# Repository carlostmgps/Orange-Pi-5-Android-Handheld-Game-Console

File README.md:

# Orange-Pi-5-Handheld-Game-Console
Orange Pi 5 + Battery + Touch Screen + Microphone + Speaker + Fan + esp32 Custom PCB controller = AMAZING ANDROID AND LINUX GAME CONSOLE!!!!!!!

Hello I'm 12zcab,a secondary school student in HK.

# why I made this project?
Welp I'm a really big fan of retro gaming such as n64, gameboy, nes,gba(oh yah I loved Nintendo.) why? That's mainly because one day I found a few old books on a table near my home labeled "Free",and I took it home and read all of it.
Theres one that caused me to be a retro fan,an user manual of Hektor,a 8085 computer.After reading that book,I discovered Zilog80,an amazing and neat perfect and the easiest design I have ever seen.
You know what? Actually the Nintendo Gameboy's instruction set is really similar to Zilog80 and I started to research on how gameboy works and I even made my "own gameboy emulator" by searching how it works online and copy some of other's code then add more function myself.
Also I like to read code of the disassembled version of gameboy game Pokémon Red.
And now I really wanna make my own game console with orange pi that can emulate the Nintendo Game Console Series from NES to NDS.

# 3/7/2026 Day 1
 12:35pm
I just discovered the blueprint scheme a few days ago and now I realized,its the time to make my dream game console come true.
There are only 2 weeks left for me but I think i can make it in time.
So firstly my planned hardware should include:
1 Orange Pi 5 16gb ram    for games like MineCraft and emulators like RETROARCH
1 touchscreen
1 speaker ...or maybe 2?
1 Microphone
1 simple tiny fan to cool down my CM5
2 D1mini for my custom PCB comtroller
2 Joysticks
IDK A few buttons
Some Batteries

My goal:
1.Use linux to run minecraft Java
2.Use retroarch to emulate NDS Games

USB Battery Pack for Raspberry Pi - 10000mAh - 2 x 5V outputs  [LINK](https://www.adafruit.com/product/1566) 39.95USD
Orange Pi 5 16gb [Link](https://e.tb.cn/h.i2LfNGjXf5lZXff?tk=K51dUuX3cC2)  1900 rmb
2x 64gb tfcard [LINK](https://e.tb.cn/h.i2ybQZQlsHyMiE1?tk=S8PhUuRI9QB)  140rmb
7inch touchscreen [Link](https://e.tb.cn/h.i2RoroSwYrMQFAG?tk=mAtMUuRFne7) 198rmb
Cooling Fan 19rmb [LINK](https://e.tb.cn/h.idzK3fJlqxSjamQ?tk=dNAvUuRyINo)

Then I started designing my d1mini joycon😜😜(18:25pm)

Erm yah I just wired the power supply and watched some youtube and now is 23:58pm and I guess I gotta sleep.

# Day 2 8-3-2026  17:35
Humm I decided to use esp32 C3 supermini board I found in taobao as it's much smaller.
However...I really can't find a Kicad module so I use Conn_MMxNN to represent the board.
23:45 YEAH~~~~ I think this kinda good i guess

12:49am gotta sleep :/ I just finished routing the pcb😁😁

# Day 3 9-3-2026
Continued on pcb editing and searched for material needed in taobao website.

Also I hope I can finish the pcb design in 3 to 4days and prepare the material list in a week then start to design the case.
Hopefully I can submit the project for review before 23-3-2026.

# Day 6 12-3-2026
I just done a simple bom list and finished all the pcb designing(oh yeah it's name was d1mini joycon as I originally wanted to use d1mini but found out it only have 1 analog pin) (yay!) All files including the stl file can be found in the PCB-Design folder in github.
Erm because I'm lazy so I think i will just simply flip the board for another side hehe.
Also I just did some research on using esp32 to make controllers and I tried it with d1mini and it's perfect:D

# Day 11 17-3-2026
HUMMMMMMMM I hope this 3D model is okay I guess. Im not really good at designing.

The 3D model is uploaded to the Model file,but sadly i cant really share the original file cuz its made with tinkercad.
[LINK to TINKERCAD Project](https://www.tinkercad.com/things/lrAWRHE2oKm-orangepi-game-console?sharecode=MQfT5zH1kE5UchqxLdm9KHmoapcb7OkEz_jWbnckgjE)

# Day 13 19-3-2026
YAY i just done the firmware,however the usage of S and S2 button and Mode button and LED is not yet decided yet :D
I have made two different firmware files,for arduino and micropython.
Actually I'm not really good at arduino CPP coding but i think it does save more memory incase i wanna make a macro function to record my move and save them which may use a lot of memory?
[LINK to the firmware file](https://github.com/carlostmgps/Orange-Pi-5-Android-Handheld-Game-Console/tree/main/firmware)

Erm the submission is reject then I think i will try to save money and buy the orange pi myself later 😅😅
I deleted the orange pi and it's fan from bom and tried to resubmit:D

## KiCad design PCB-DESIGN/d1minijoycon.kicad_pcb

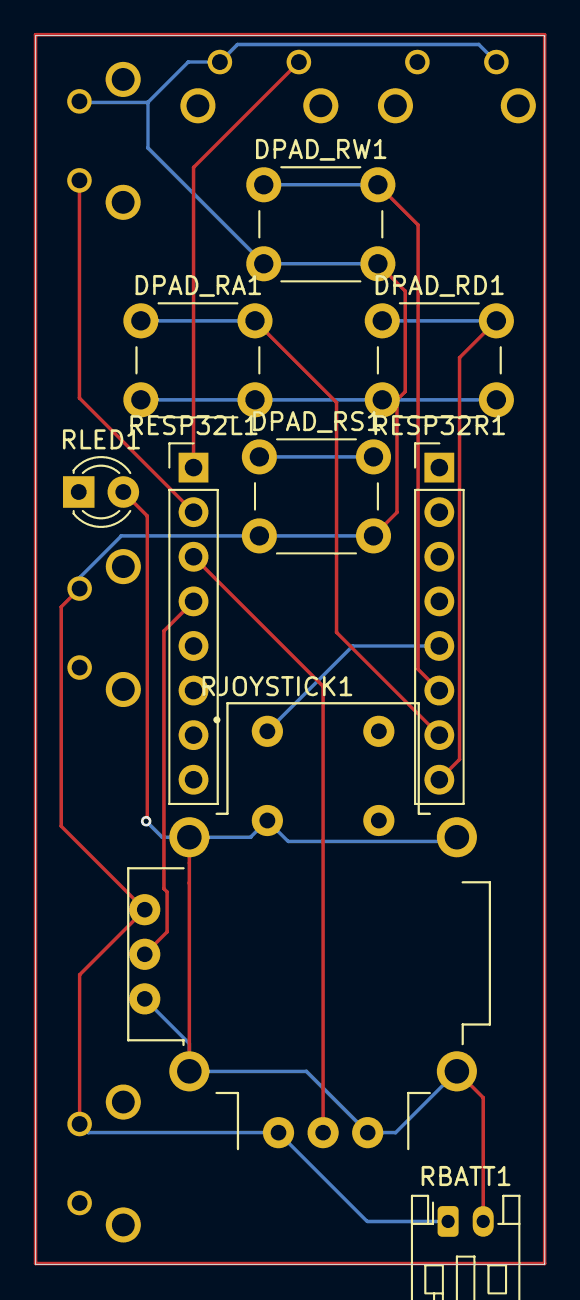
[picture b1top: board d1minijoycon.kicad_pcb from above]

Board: 2 copper layers, 29.0 x 70.0 mm, 14 parts (0 on the bottom side), 10 nets.

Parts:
DPAD_RA1: A; SW_PUSH_6mm_H5mm
DPAD_RD1: D; SW_PUSH_6mm_H5mm
DPAD_RS1: S; SW_PUSH_6mm_H5mm
DPAD_RW1: W; SW_PUSH_6mm_H5mm
R2S1: S2; TACT-6MM-HOR
RBATT1: Conn_01x02; JST_PH_S2B-PH-K_1x02_P2.00mm_Horizontal
RESP32L1, RESP32R1: ESP32 C3 SUPERMINI; PinHeader_1x08_P2.54mm_Vertical
RJOYSTICK1: COM-09032; XDCR_COM-09032
RL1: L; TACT-6MM-HOR
RLED1: LED; LED_D3.0mm
RM1: MODE; TACT-6MM-HOR
RR1: R; TACT-6MM-HOR
RS1: S; TACT-6MM-HOR

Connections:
unnamed: DPAD_RA1.2, DPAD_RD1.2, DPAD_RS1.2, DPAD_RW1.2, R2S1.2, RBATT1.1, RJOYSTICK1.H1 (H+), RJOYSTICK1.V1 (V+), RL1.2, RM1.1, RR1.2, RS1.2
unnamed: RBATT1.2, RJOYSTICK1.B2A (SEL-), RJOYSTICK1.H3 (H-), RJOYSTICK1.S1 (SHIELD), RJOYSTICK1.S2 (SHIELD), RJOYSTICK1.S3 (SHIELD), RJOYSTICK1.S4 (SHIELD), RJOYSTICK1.V3 (V-), RLED1.2 (A)
unnamed: RESP32L1.4, RJOYSTICK1.V2 (V)
unnamed: RESP32L1.3 (Pin_5), RJOYSTICK1.H2 (H)
unnamed: RESP32L1.2 (Pin_6), RR1.1
unnamed: RESP32L1.1 (Pin_7), RM1.2
unnamed: RESP32R1.5 (Pin_1), RJOYSTICK1.B1A (SEL+)
unnamed: DPAD_RW1.1, RESP32R1.6 (Pin_2)
unnamed: DPAD_RA1.1, RESP32R1.7 (Pin_3)
unnamed: DPAD_RD1.1, RESP32R1.8 (Pin_4)

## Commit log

2026-03-08 Rename d1minijoycon.png to image/d1minijoycon.png
2026-03-08 Update README with routed PCB images
    Added images of the routed PCB to the README.
2026-03-09 更新 README.md
2026-03-12 Create EASTEREGGHEHE
2026-03-17 Revise project timeline and add 3D model information
    Updated project timeline and added new sections for Day 11 and 3D model details.
2026-03-17 Rename OrangePi Game Console.stl to Model/OrangePi Game Console.stl
2026-03-17 Create erm another easteregg
2026-03-19 Fix formatting and capitalization in README.md
    Fixed formatting issues in the README file, including spacing and capitalization.
2026-03-19 Rename BOM_old.csv to BOM.csv
2026-03-19 Enhance README with firmware details and submission update
    Updated README with additional notes about firmware and submission.
